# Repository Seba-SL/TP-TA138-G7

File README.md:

Grupo 7 

Integrantes:
- Mántaras, Ramiro, , 
- Flores, Ahmed Ali, 106238, aaflores@fi.uba.ar
- Lazo, Sebastian Nahuel, 106213, slazo@fi.uba.ar

Paso 1: Clonar Repositorio en su compu
```bash
git clone https://github.com/usuario/repositorio.git
```

Paso 2: Cada vez que alguien modifique el proyecto, actualizar:
```bash
git pull
```
Paso 3: Cada vez que uno trabaje en el proyecto, subir los cambios (importante actualizar antes):
```bash
git add .
git commit -m "mensaje de que se hizo"
git push
```

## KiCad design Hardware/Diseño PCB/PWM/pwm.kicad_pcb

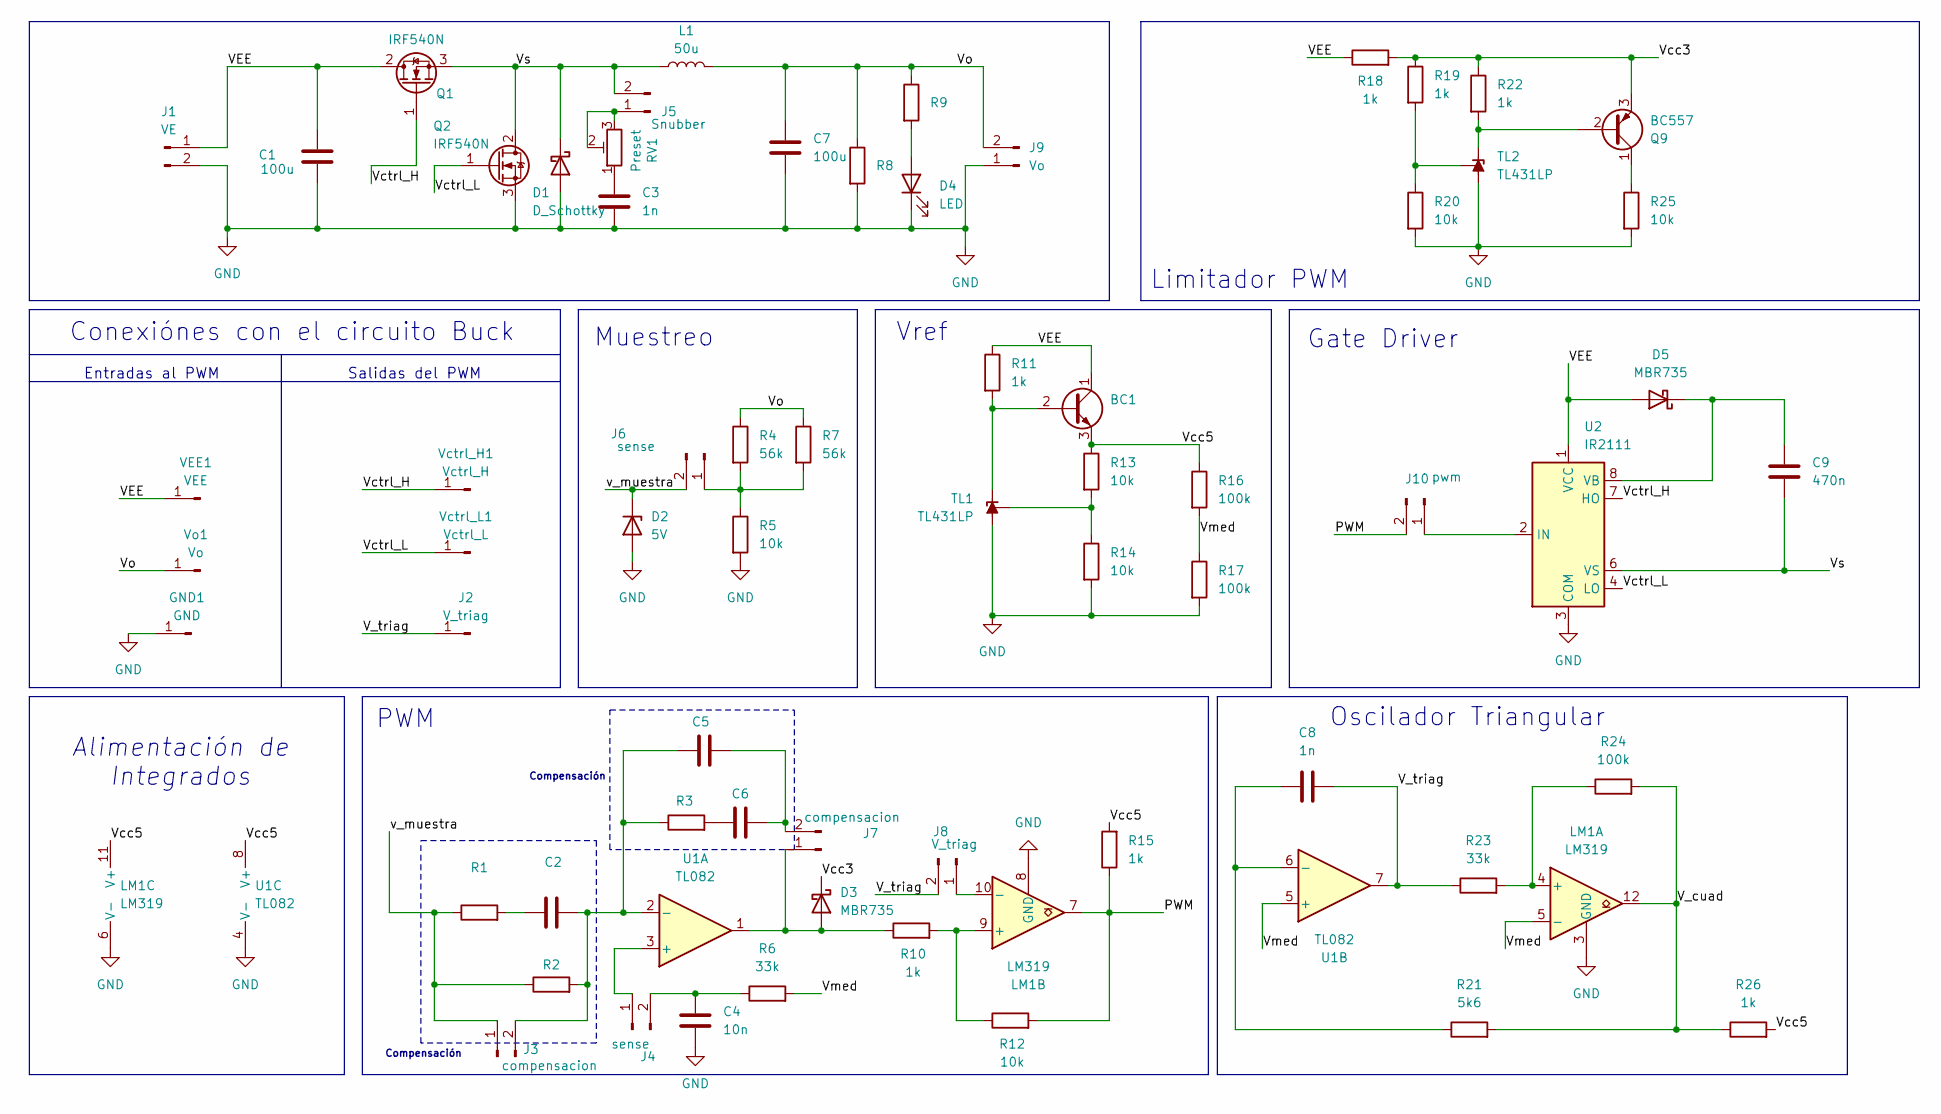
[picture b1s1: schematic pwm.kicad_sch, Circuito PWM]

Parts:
BC1: TO-92_HandSolder
C1, C7: 100u; CP_Radial_D10.0mm_P2.50mm
C2, C8: 1n; C_Disc_D6.0mm_W4.4mm_P5.00mm
C3: 1n; C_Disc_D3.0mm_W2.0mm_P2.50mm
C4, C5, C6: 10n; C_Disc_D6.0mm_W4.4mm_P5.00mm
C9: 470n; C_Disc_D6.0mm_W4.4mm_P5.00mm
D1: D_Schottky; D_DO-201AD_P12.70mm_Horizontal
D2: 5V; D_DO-34_SOD68_P7.62mm_Horizontal
D3, D5: MBR735; D_A-405_P7.62mm_Horizontal
D4: LED; LED_D4.0mm
GND1: GND; PinHeader_1x01_P2.00mm_Vertical
J1: VE; TerminalBlock_Phoenix_MKDS-1,5-2_1x02_P5.00mm_Horizontal
J2: V_triag; PinHeader_1x01_P2.00mm_Vertical
J3, J7: compensacion; PinHeader_1x02_P2.00mm_Vertical
J4, J6: sense; PinHeader_1x02_P2.00mm_Vertical
J5: Snubber; PinHeader_1x02_P2.00mm_Vertical
J8: V_triag; PinHeader_1x02_P2.00mm_Vertical
J9: Vo; TerminalBlock_Phoenix_MKDS-1,5-2_1x02_P5.00mm_Horizontal
J10: pwm; PinHeader_1x02_P2.00mm_Vertical
L1: 50u; EE19
LM1: LM319; DIP-14_W7.62mm_Socket
Q1, Q2: IRF540N; TO-220-3_Vertical
Q9: BC557; TO-92_Wide
R1, R5, R12, R13, R14, R20, R25: 10k; R_Axial_DIN0204_L3.6mm_D1.6mm_P7.62mm_Horizontal
R2: 30k; R_Axial_DIN0204_L3.6mm_D1.6mm_P7.62mm_Horizontal
R3, R6, R23: 33k; R_Axial_DIN0204_L3.6mm_D1.6mm_P7.62mm_Horizontal
R4, R7: 56k; R_Axial_DIN0204_L3.6mm_D1.6mm_P7.62mm_Horizontal
R8: R_Axial_DIN0414_L11.9mm_D4.5mm_P15.24mm_Horizontal
R9: R_Axial_DIN0204_L3.6mm_D1.6mm_P7.62mm_Horizontal
R10, R11, R15, R18, R19, R22, R26: 1k; R_Axial_DIN0204_L3.6mm_D1.6mm_P7.62mm_Horizontal
R16, R17, R24: 100k; R_Axial_DIN0204_L3.6mm_D1.6mm_P7.62mm_Horizontal
R21: 5k6; R_Axial_DIN0204_L3.6mm_D1.6mm_P7.62mm_Horizontal
RV1: Preset; Potentiometer_Bourns_3386P_Vertical
TL1, TL2: TL431LP; TO-92_HandSolder
U1: TL082; DIP-8_W7.62mm_Socket
U2: IR2111; DIP-8_W7.62mm_Socket
VEE1: VEE; PinHeader_1x01_P2.00mm_Vertical
Vctrl_H1: Vctrl_H; PinHeader_1x01_P2.00mm_Vertical
Vctrl_L1: Vctrl_L; PinHeader_1x01_P2.00mm_Vertical
Vo1: Vo; PinHeader_1x01_P2.00mm_Vertical

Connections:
/PWM: J10.2, LM1.7, R12.2, R15.1
/VEE: BC1.1 (C), C1.1, D5.2 (A), J1.1, Q1.2 (D), R11.1, R18.1, U2.1 (VCC), VEE1.1 (Pin_1_1)
/V_cuad: LM1.12, R21.2, R24.2, R26.1
/V_triag: C8.2, J2.1 (Pin_1_1), J8.2, R23.1, U1.7
/Vcc3: D3.1 (K), Q9.3 (E), R18.2, R19.1, R22.1
/Vcc5: BC1.3 (E), LM1.11 (V+), R13.1, R15.2, R16.1, R26.2, U1.8 (V+)
/Vctrl_H: Q1.1 (G), U2.7 (HO), Vctrl_H1.1 (Pin_1_1)
/Vctrl_L: Q2.1 (G), U2.4 (LO), Vctrl_L1.1 (Pin_1_1)
/Vmed: LM1.5 (-), R6.2, R16.2, R17.1, U1.5 (+)
/Vo: C7.1, J9.2, L1.2, R4.1, R7.1, R8.1, R9.1, Vo1.1 (Pin_1_1)
/Vs: C9.2, D1.1 (K), J5.2, L1.1, Q1.3 (S), Q2.2 (D), U2.6 (VS)
/v_muestra: D2.1 (K), J3.1, J6.2, R1.1, R2.1
GND: C1.2, C3.2, C4.1, C7.2, D1.2 (A), D2.2 (A), D4.1 (K), GND1.1 (Pin_1_1), J1.2, J9.1, LM1.3 (GND), LM1.6 (V-), LM1.8 (GND), Q2.3 (S), R5.2, R8.2, R14.2, R17.2, R20.2, R25.2, TL1.2 (A), TL2.2 (A), U1.4 (V-), U2.3 (COM)
unnamed: BC1.2 (B), R11.2, TL1.3 (K)
unnamed: C2.1, R1.2
unnamed: C3.1, RV1.1
unnamed: C6.1, R3.2
unnamed: D3.2 (A), J7.1, R10.1, U1.1
unnamed: D4.2 (A), R9.2
unnamed: C9.1, D5.1 (K), U2.8 (VB)
unnamed: C2.2, C5.1, J3.2, R2.2, R3.1, U1.2 (-)
unnamed: J4.1, U1.3 (+)
unnamed: C4.2, J4.2, R6.1
unnamed: J5.1, RV1.2, RV1.3
unnamed: J6.1, R4.2, R5.1, R7.2
unnamed: C5.2, C6.2, J7.2
unnamed: J8.1, LM1.10 (-)
unnamed: J10.1, U2.2 (IN)
unnamed: LM1.4 (+), R23.2, R24.1
unnamed: LM1.9 (+), R10.2, R12.1
unnamed: Q9.2 (B), R22.2, TL2.3 (K)
unnamed: Q9.1 (C), R25.1
unnamed: R13.2, R14.1, TL1.1 (REF)
unnamed: R19.2, R20.1, TL2.1 (REF)
unnamed: C8.1, R21.1, U1.6 (-)

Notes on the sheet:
Limitador PWM
Conexiónes con el circuito Buck
Vref
Salidas del PWM
Compensación
Oscilador Triangular
Entradas al PWM
Gate Driver
Alimentación de Integrados
PWM
Muestreo

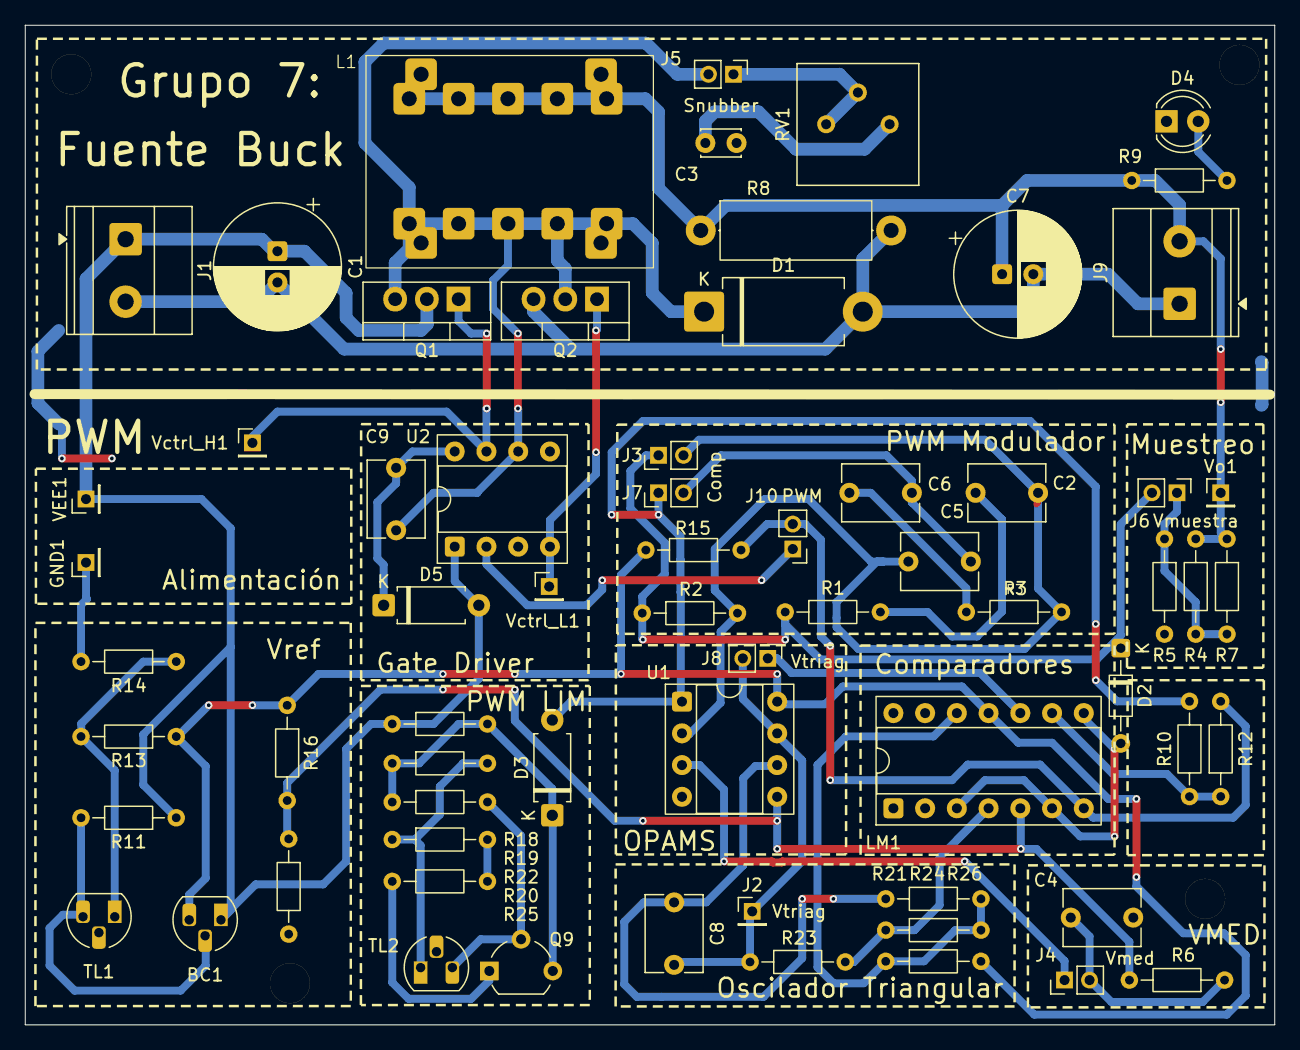
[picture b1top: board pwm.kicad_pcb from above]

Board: 2 copper layers, 100.0 x 80.0 mm, 66 parts (0 on the bottom side), 35 nets.

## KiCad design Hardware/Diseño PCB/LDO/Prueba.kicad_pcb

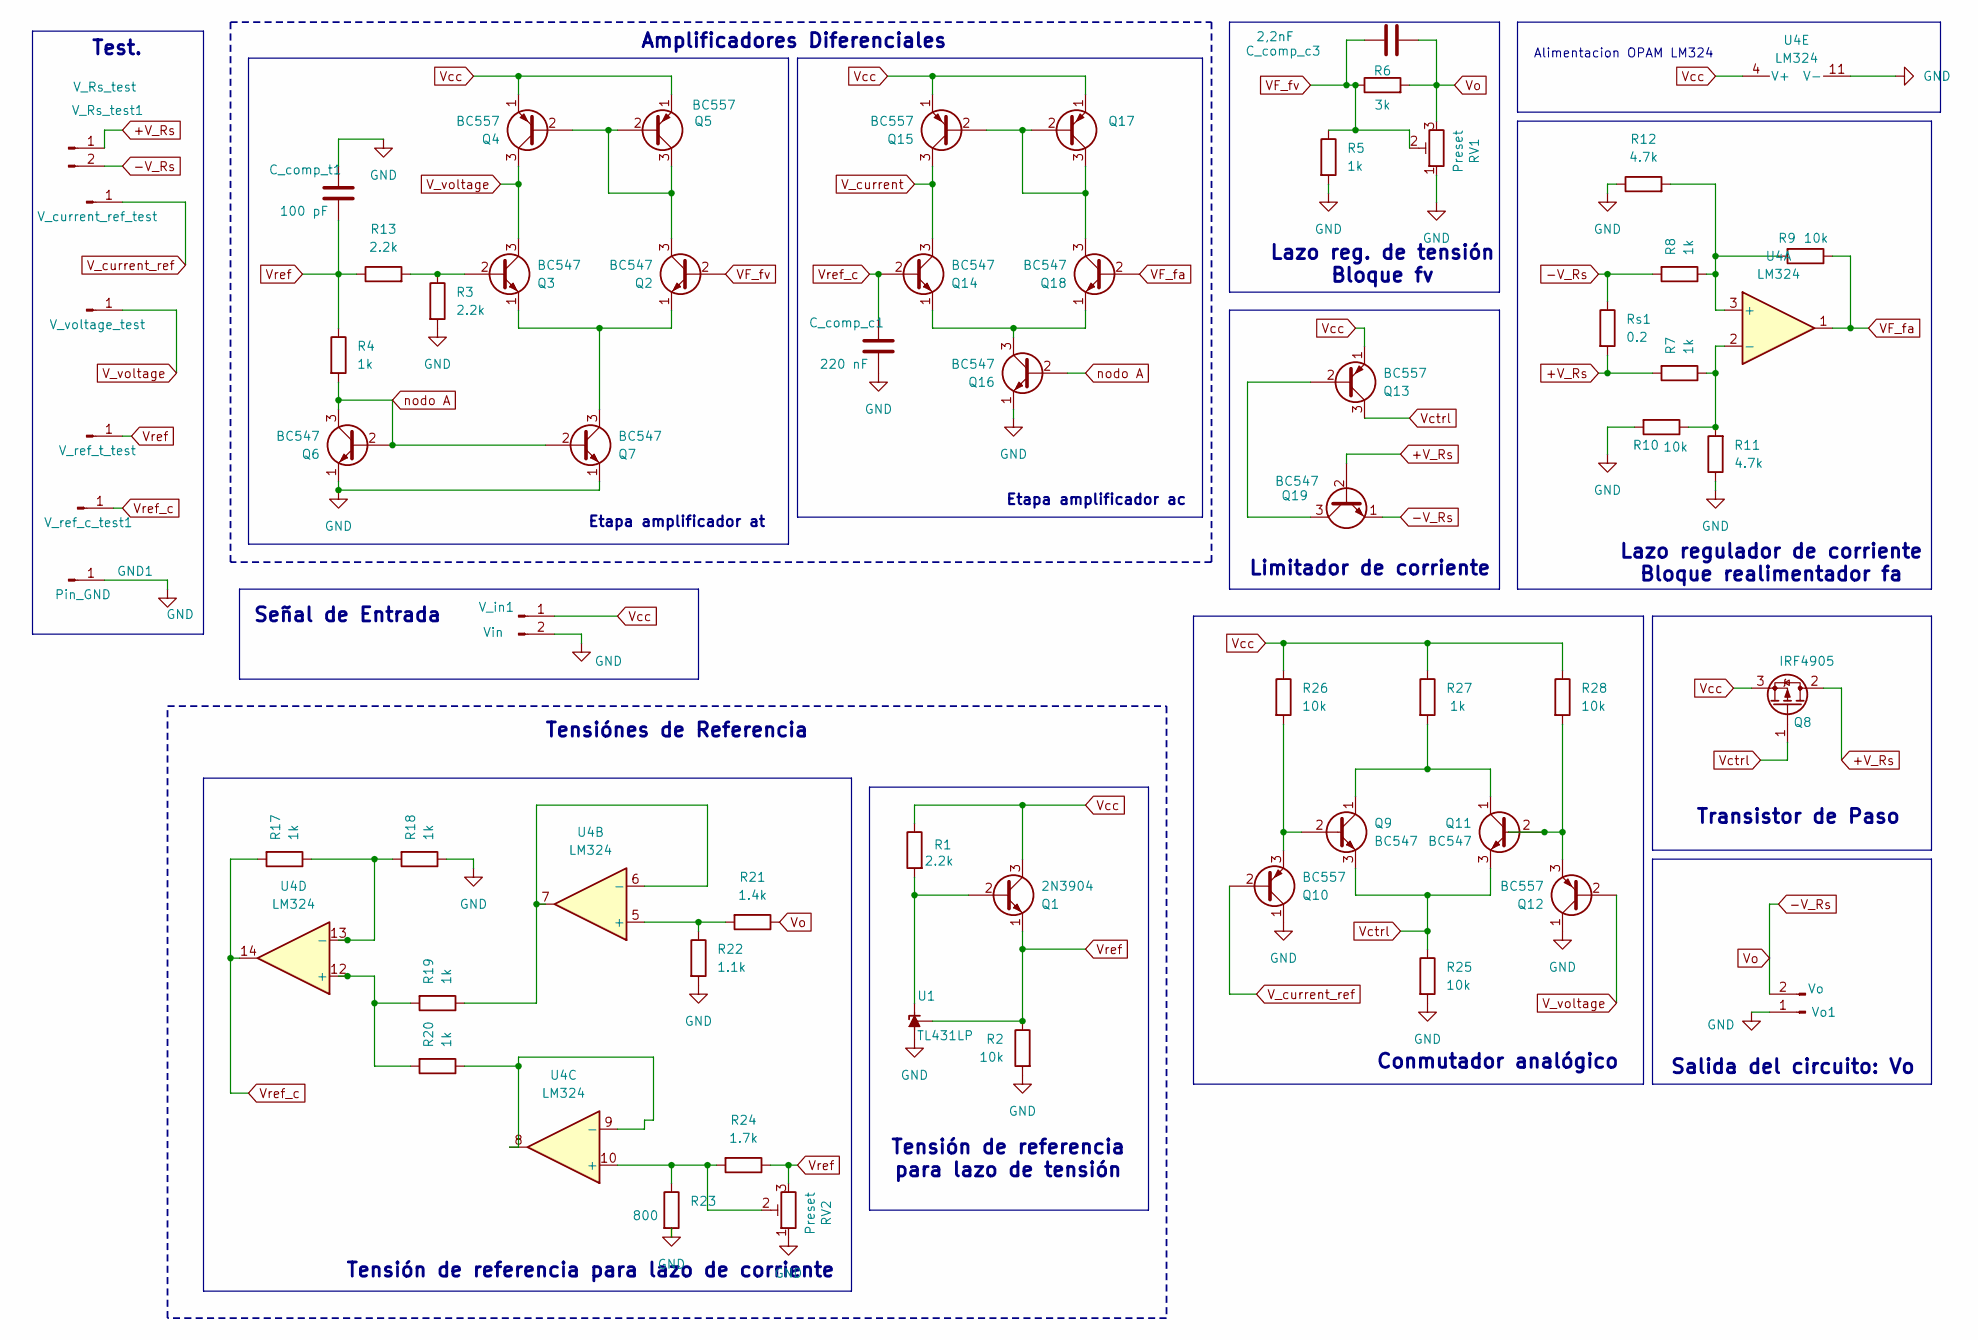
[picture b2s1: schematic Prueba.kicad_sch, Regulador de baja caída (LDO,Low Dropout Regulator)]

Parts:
C_comp_c1: 220 nF; C_Disc_D3.8mm_W2.6mm_P2.50mm
C_comp_c3: 2,2nF; C_Disc_D3.8mm_W2.6mm_P2.50mm
C_comp_t1: 100 pF; C_Disc_D3.8mm_W2.6mm_P2.50mm
GND1: Pin_GND; PinHeader_1x01_P2.00mm_Vertical
GND2: V_ref_c_test1; PinHeader_1x01_P2.00mm_Vertical
GND3: V_ref_t_test; PinHeader_1x01_P2.00mm_Vertical
GND4: V_voltage_test; PinHeader_1x01_P2.00mm_Vertical
GND5: V_current_ref_test; PinHeader_1x01_P2.00mm_Vertical
Q1: 2N3904; TO-92_Inline
Q2, Q3, Q6, Q7, Q9, Q11, Q14, Q16, Q18, Q19: BC547; TO-92_Inline
Q4, Q5, Q10, Q12, Q13, Q15, Q17: BC557; TO-92_Inline
Q8: IRF4905; TO-220-3_Vertical
R1, R3, R13: 2.2k; R_Axial_DIN0204_L3.6mm_D1.6mm_P7.62mm_Horizontal
R2, R9, R10, R25, R26, R28: 10k; R_Axial_DIN0204_L3.6mm_D1.6mm_P7.62mm_Horizontal
R4, R5, R7, R8, R17, R18, R19, R20, R27: 1k; R_Axial_DIN0204_L3.6mm_D1.6mm_P7.62mm_Horizontal
R6: 3k; R_Axial_DIN0204_L3.6mm_D1.6mm_P7.62mm_Horizontal
R11, R12: 4.7k; R_Axial_DIN0204_L3.6mm_D1.6mm_P7.62mm_Horizontal
R21: 1.4k; R_Axial_DIN0204_L3.6mm_D1.6mm_P7.62mm_Horizontal
R22: 1.1k; R_Axial_DIN0204_L3.6mm_D1.6mm_P7.62mm_Horizontal
R23: 800; R_Axial_DIN0204_L3.6mm_D1.6mm_P7.62mm_Horizontal
R24: 1.7k; R_Axial_DIN0204_L3.6mm_D1.6mm_P7.62mm_Horizontal
RV1, RV2: Preset; Potentiometer_Bourns_3266W_Vertical
Rs1: 0.2; R_Axial_DIN0204_L3.6mm_D1.6mm_P7.62mm_Horizontal
U1: TL431LP; TO-92_Inline
U4: LM324; DIP-14_W10.16mm_LongPads
V_Rs_test1: V_Rs_test; PinHeader_1x02_P2.00mm_Vertical
V_in1: Vin; TerminalBlock_MaiXu_MX126-5.0-02P_1x02_P5.00mm
Vo1: Vo; TerminalBlock_MaiXu_MX126-5.0-02P_1x02_P5.00mm

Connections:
+V_Rs: Q8.2 (D), Q19.2 (B), R7.2, Rs1.2, V_Rs_test1.1; also elsewhere on the board
-V_Rs: C_comp_c3.2, Q19.1 (E), R6.2, R8.2, R21.1, RV1.3, Rs1.1, V_Rs_test1.2, Vo1.2; also elsewhere on the board
GND: C_comp_c1.2, C_comp_t1.1, GND1.1 (Pin_1_1), Q6.1 (E), Q7.1 (E), Q10.1 (C), Q12.1 (C), Q16.1 (E), R2.2, R3.2, R5.2, R10.2, R11.1, R12.1, R18.1, R22.2, R23.2, R25.2, RV1.1, RV2.1, U1.2 (A), U4.11 (V-), V_in1.2, Vo1.1
unnamed: Q1.2 (B), R1.2, U1.3 (K)
unnamed: Q2.3 (C), Q4.2 (B), Q5.2 (B), Q5.3 (C)
unnamed: Q2.1 (E), Q3.1 (E), Q7.3 (C)
unnamed: Q3.2 (B), R3.1, R13.2
unnamed: Q9.2 (B), Q10.3 (E), R26.2
unnamed: Q11.2 (B), Q12.3 (E), R28.2
unnamed: Q9.1 (C), Q11.1 (C), R27.2
unnamed: Q13.2 (B), Q19.3 (C)
unnamed: Q14.1 (E), Q16.3 (C), Q18.1 (E)
unnamed: Q15.2 (B), Q17.2 (B), Q17.3 (C), Q18.3 (C)
unnamed: R8.1, R9.2, R12.2, U4.3 (+)
unnamed: R7.1, R10.1, R11.2, U4.2 (-)
unnamed: R21.2, R22.1, U4.5 (+)
unnamed: R19.1, U4.6 (-), U4.7
unnamed: R23.1, R24.2, RV2.2, U4.10 (+)
unnamed: R20.1, U4.8, U4.9 (-)
unnamed: R19.2, R20.2, U4.12 (+)
unnamed: R17.1, R18.2, U4.13 (-)
VF_fa: Q18.2 (B), R9.1, U4.1
VF_fv: C_comp_c3.1, Q2.2 (B), R5.1, R6.1, RV1.2
V_current: Q14.3 (C), Q15.3 (C)
V_current_ref: GND5.1, Q10.2 (B); also elsewhere on the board
V_voltage: GND4.1, Q3.3 (C), Q4.3 (C), Q12.2 (B); also elsewhere on the board
Vcc: Q1.3 (C), Q4.1 (E), Q5.1 (E), Q8.3 (S), Q13.1 (E), Q15.1 (E), Q17.1 (E), R1.1, R26.1, R27.1, R28.1, U4.4 (V+), V_in1.1
Vctrl: Q8.1 (G), Q9.3 (E), Q11.3 (E), Q13.3 (C), R25.1
Vref: C_comp_t1.2, GND3.1, Q1.1 (E), R2.1, R4.1, R13.1, R24.1, RV2.3, U1.1 (REF); also elsewhere on the board
Vref_c: C_comp_c1.1, GND2.1, Q14.2 (B), R17.2, U4.14; also elsewhere on the board
nodo A: Q6.2 (B), Q6.3 (C), Q7.2 (B), Q16.2 (B), R4.2

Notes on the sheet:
Etapa amplificador at
Lazo reg. de tensión Bloque fv
Tensión de referencia para lazo de corriente
Transistor de Paso
Limitador de corriente
Conmutador analógico
Amplificadores Diferenciales
Tensión de referencia para lazo de tensión
Test.
Tensiónes de Referencia
Etapa amplificador ac
Señal de Entrada
Salida del circuito: Vo
Alimentacion OPAM LM324
Lazo regulador de corriente Bloque realimentador fa

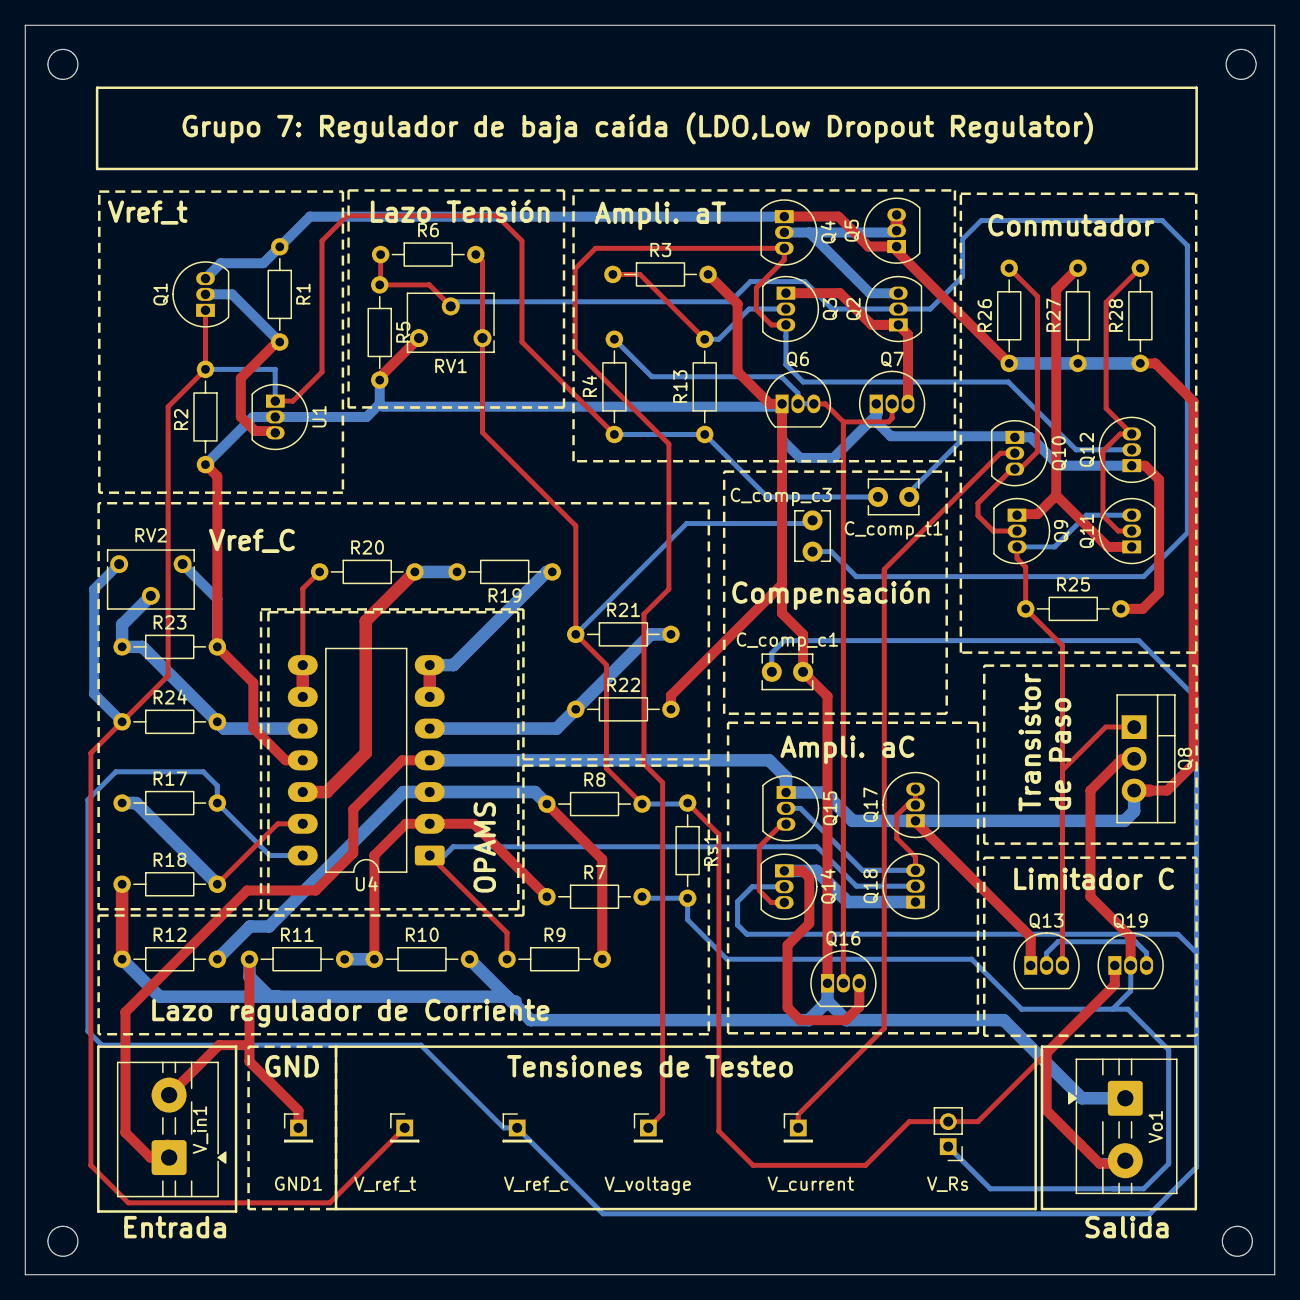
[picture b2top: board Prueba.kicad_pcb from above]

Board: 2 copper layers, 100.0 x 100.0 mm, 60 parts (0 on the bottom side), 31 nets.

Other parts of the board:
V_Rs: V_Rs_test; PinHeader_1x02_P2.00mm_Vertical
V_current: V_current_test; PinHeader_1x01_P2.00mm_Vertical
V_ref_c: V_ref_c_test; PinHeader_1x01_P2.00mm_Vertical
V_ref_t: V_ref_test; PinHeader_1x01_P2.00mm_Vertical
V_voltage: V_voltage_test; PinHeader_1x01_P2.00mm_Vertical

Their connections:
+V_Rs: V_Rs.1; also elsewhere on the board
-V_Rs: V_Rs.2; also elsewhere on the board
V_current_ref: V_current.1 (Pin_1_1); also elsewhere on the board
V_voltage: V_voltage.1 (Pin_1_1); also elsewhere on the board
Vref: V_ref_t.1 (Pin_1_1); also elsewhere on the board
Vref_c: V_ref_c.1 (Pin_1_1); also elsewhere on the board

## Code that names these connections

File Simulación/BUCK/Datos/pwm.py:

import pandas as pd
import matplotlib.pyplot as plt
import numpy as np

# Cargar los datos
pwm = pd.read_csv('pwm.txt', sep='\t')
pwm2 = pd.read_csv('pwm2.txt', sep='\t')

# Convertir la columna de tiempo a microsegundos para mejor legibilidad
pwm['time_us'] = pwm['time'] * 1e6
pwm2['time_us'] = pwm2['time'] * 1e6

# Encontrar el punto medio
mid_index = len(pwm) // 2
mid_time = pwm.iloc[mid_index]['time_us']

# Definir la ventana de 20 microsegundos alrededor del punto medio
window_width = 20  # microsegundos
t_min = mid_time - window_width / 2
t_max = mid_time + window_width / 2

# Filtrar datos dentro de la ventana
pwm_window = pwm[(pwm['time_us'] >= t_min) & (pwm['time_us'] <= t_max)]
pwm2_window = pwm2[(pwm2['time_us'] >= t_min) & (pwm2['time_us'] <= t_max)]

# Crear figura con subgráficos
fig, axes = plt.subplots(2, 1, figsize=(12, 8))

# Gráfico 1: PWM - V(v_cuad) y V(v_triag)
ax1 = axes[0]
ax1.plot(pwm_window['time_us'], pwm_window['V(v_cuad)'], 'b-', linewidth=1.5, label='V(v_cuad)')
ax1.plot(pwm_window['time_us'], pwm_window['V(v_triag)'], 'r-', linewidth=1.5, label='V(v_triag)')
ax1.set_xlabel('Tiempo (µs)')
ax1.set_ylabel('Voltaje (V)')
ax1.set_title('Oscilador triangular')
ax1.grid(True, alpha=0.3)
ax1.legend()

# Gráfico 2: PWM2 - V(pwm), V(v_triag), V(vmed), V(n003)
pwm2_filtered = pwm2[(pwm2['time_us'] >= 200) & (pwm2['time_us'] <= 300)]
ax2 = axes[1]
ax2.plot(pwm2_filtered['time_us'], pwm2_filtered['V(pwm)'], 'b-', linewidth=1.5, label='V(pwm)')
ax2.plot(pwm2_filtered['time_us'], pwm2_filtered['V(v_triag)'], 'r-', linewidth=1.5, label='V(v_triag)')
ax2.plot(pwm2_filtered['time_us'], pwm2_filtered['V(vmed)'], 'g-', linewidth=1.5, label='V(vmed)')
ax2.plot(pwm2_filtered['time_us'], pwm2_filtered['V(n003)'], 'm-', linewidth=1.5, label='V(Av*v_sense)')
ax2.set_xlabel('Tiempo (µs)')
ax2.set_ylabel('Voltaje (V)')
ax2.set_title('PWM2 - Múltiples Señales')
ax2.grid(True, alpha=0.3)
ax2.legend()

plt.tight_layout()

# Guardar gráficos
fig1 = plt.figure(figsize=(12, 5))
ax_pwm = fig1.add_subplot(111)
ax_pwm.plot(pwm_window['time_us'], pwm_window['V(v_cuad)'], 'b-', linewidth=1.5, label='V(v_cuad)')
ax_pwm.plot(pwm_window['time_us'], pwm_window['V(v_triag)'], 'r-', linewidth=1.5, label='V(v_triag)')
ax_pwm.set_xlabel('Tiempo (µs)')
ax_pwm.set_ylabel('Voltaje (V)')
ax_pwm.set_title('PWM - Señales de PWM y Triangular')
ax_pwm.grid(True, alpha=0.3)
ax_pwm.legend()
fig1.savefig('grafico_pwm.png', dpi=150, bbox_inches='tight')
plt.close(fig1)

fig2 = plt.figure(figsize=(12, 5))
ax_pwm2 = fig2.add_subplot(111)
ax_pwm2.plot(pwm2_filtered['time_us'], pwm2_filtered['V(pwm)'], 'b-', linewidth=1.5, label='V(pwm)')
ax_pwm2.plot(pwm2_filtered['time_us'], pwm2_filtered['V(v_triag)'], 'r-', linewidth=1.5, label='V(v_triag)')
ax_pwm2.plot(pwm2_filtered['time_us'], pwm2_filtered['V(vmed)'], 'g-', linewidth=1.5, label='V(vmed)')
ax_pwm2.plot(pwm2_filtered['time_us'], pwm2_filtered['V(n003)'], 'm-', linewidth=1.5, label='V(Av*v_sense)')
ax_pwm2.set_xlabel('Tiempo (µs)')
ax_pwm2.set_ylabel('Voltaje (V)')
ax_pwm2.set_title('Señal de salida PWM')
ax_pwm2.grid(True, alpha=0.3)
ax_pwm2.legend()
fig2.savefig('grafico_pwm2.png', dpi=150, bbox_inches='tight')
plt.close(fig2)

# Imprimir información
print(f"Datos cargados correctamente:")
print(f"  PWM: {len(pwm)} puntos, tiempo total: {pwm['time_us'].min():.2f} - {pwm['time_us'].max():.2f} µs")
print(f"  PWM2: {len(pwm2)} puntos, tiempo total: {pwm2['time_us'].min():.2f} - {pwm2['time_us'].max():.2f} µs")
print(f"\nVentana mostrada:")
print(f"  PWM: {t_min:.2f} - {t_max:.2f} µs (punto medio: {mid_time:.2f} µs) - {len(pwm_window)} puntos")
print(f"  PWM2: 200.00 - 300.00 µs - {len(pwm2_filtered)} puntos")
print(f"\nGráficos guardados:")
print(f"  - grafico_pwm.png")
print(f"  - grafico_pwm2.png")

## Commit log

2026-03-15 inicio
2026-03-15 Format README.md with code blocks and clean up
2026-03-15 Update README.md with group information
2026-03-15 Ejemplo hoja de presupuesto
2026-03-20 prueba archivo kicad
2026-03-27 Simulación 27/03
2026-03-27 modelo TL431
2026-03-28 Agregadas Datasheets
2026-03-28 Actualización simulación LDO
2026-03-28 Actualización simulación
2026-03-28 Modelo TL431.spi
2026-03-28 Agregue simbolo del TL431, y junto al modelo , pero todavia no logre los 2.5 V desde el TL431
2026-03-28 TL431 ok , vref
2026-03-28 Comentarios para medir reg linea, carga y eficiencia
2026-03-28 Simulacion de reg de carga y de linea
2026-03-28 Agregue latex con informe
2026-04-04 Implementación inicial de lazo de corriente (No funcional))
2026-04-05 Lazos funcionando en conjunto
2026-04-07 titulos en bloques
2026-04-07 Esquematico en EtapasdelDiseño/diseñocircuital
2026-04-07 Vref y amplificador en esquemtico
2026-04-07 Vref y amplificador en esquemtico 2
2026-04-07 Bloque aparte para el lazo de reg de corriente, tome referencias de Rs
2026-04-07 lazo de corriente y vref_current en esquematico
2026-04-07 Esquematico con conmutador analógico, informe
2026-04-07 Puntos de testeo, en esquematico
2026-04-07 Agregada elección del transistor al informe
2026-04-08 esquema gral en informe
2026-04-08 informe
2026-04-08 Avances en informe
2026-04-08 Ajustes lazo de corriente
2026-04-08 Explicación previa reg tensión , reg corriente y vrefs
2026-04-08 Diagrama general
2026-04-08 informe 15:30
2026-04-08 Apartado para graficos a partir de scripts de python y datos de ltspice
2026-04-08 Graficos con simulaciónes. provisorio
2026-04-08 Mejora Script unico para graficos de LDO
2026-04-08 Organizacion carpetas de simulación
2026-04-08 Agregue esquematicos en apendices
2026-04-09 Agregado Scrip V vs I
    Modificar para emprolijar
2026-04-09 cambios_conclusiones
2026-04-09 Avances y reestructuraciónes del informe
2026-04-10 informe: Vo, Vcc en funcion del tiempo, comparación de componentes ac
2026-04-10 Informe , reg linea
2026-04-10 Algunas conclusiones
2026-04-10 Checkpoint1 V1
2026-04-10 Correción
2026-04-11 Agregado lazo limitador Shunt
2026-04-11 Actualizacion graficos y esquematico
2026-04-11 Agregado regulador shunt al informe y mejora de vdo
2026-04-11 Emprolijamiento del circuito
2026-04-11 Actualizacion esquematico
2026-04-11 Actualización regulación de linea : Datos + zoom
2026-04-12 Correcciones al circuito y realizadas simulaciones
2026-04-13 Checkpoint 1 V2
2026-04-18 Arreglo pares diferenciales en el esquematico
2026-04-18 Planilla de compras actualizada, hojas de datos
2026-04-18 huellas de componentes ok
2026-04-19 LM324 Agregado
2026-04-19 Agrupación de modulos en diseño de PCB
2026-04-19 Actualizacioens al informe
2026-04-20 actualizacion presupuesto estimado
2026-04-20 Diseño PCB : Test con gnd en comun
2026-04-20 Diseño PCB: Indicador de operacionales dentro de encapsulado
2026-04-20 Diseño PCB:Arreglo LM324s con 14 pines
2026-04-20 Diseño PCB
2026-04-21 Etiquetas checkpoints, facturas y presupuesto
2026-04-21 Diseño de PCB : Informe
2026-04-21 Documento estandar IPC2222 agregado
2026-04-21 PCB: Diseño
2026-04-21 Diseño PCB : Bloque testeos y Vref_t
2026-04-21 Avances en compensación
2026-04-23 Lazo de Tension compensado
2026-04-23 analsis termico
2026-04-23 Compensación del lazo de corriente
2026-04-23 Circuito completo
2026-04-23 Diseño PCB: Informe, orificos de sujeción
2026-04-23 Diseño PCB: Informe, orificos de sujeció, C de compensacion
2026-04-23 Diseño PCB: Transistores BC557/BC547 en esquematico y pcb
2026-04-23 Diseño PCB: Pistas y C compensacion en Pcb
2026-04-23 Diseño PCB: Modificacion grosor de pistas 0.8 mm
2026-04-23 Diseño PCB: informe
2026-04-23 Diseño PCB: Correcciones profe y añadi preset
2026-04-24 Diseño PCB: Disipador, modelo 3D
2026-04-24 Simulaciones dinamicas
2026-04-24 Diseño de PCB: Agregue preset lazo de corrente y compensacion de atraso de fase
2026-04-24 Arreglado analisis termico
2026-04-25 Informe y borneras
2026-04-27 Cambios menores al informe
2026-04-29 Diseño de PCB : Logo FIUBA + pistas
2026-06-11 Informe chk5
2026-06-20 Avances CHCK 5
2026-06-21 CHK5
2026-06-21 CHK5: informe
2026-06-21 CH5: Informe
2026-06-22 Avances informe y circuito
2026-06-22 Avances al informe
2026-06-23 Avances y modificaciones
2026-06-23 Avances
2026-06-25 PCB V2
2026-06-27 CHK5: informe reg de linea
2026-06-27 Avances del ultimo dia
2026-06-28 CHK5 : informe
2026-06-28 Compensacion y avances en informe
2026-06-29 Snubber y avances en compensación
2026-06-29 CHK5: informe , reg carga
2026-06-29 CHK5:informe
2026-06-30 Avances en informe general
2026-06-30 Avances en informe final
2026-06-30 Final v1
2026-06-30 Final v2
